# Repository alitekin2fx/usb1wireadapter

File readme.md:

DS2480B Based 1-Wire USB Adapter

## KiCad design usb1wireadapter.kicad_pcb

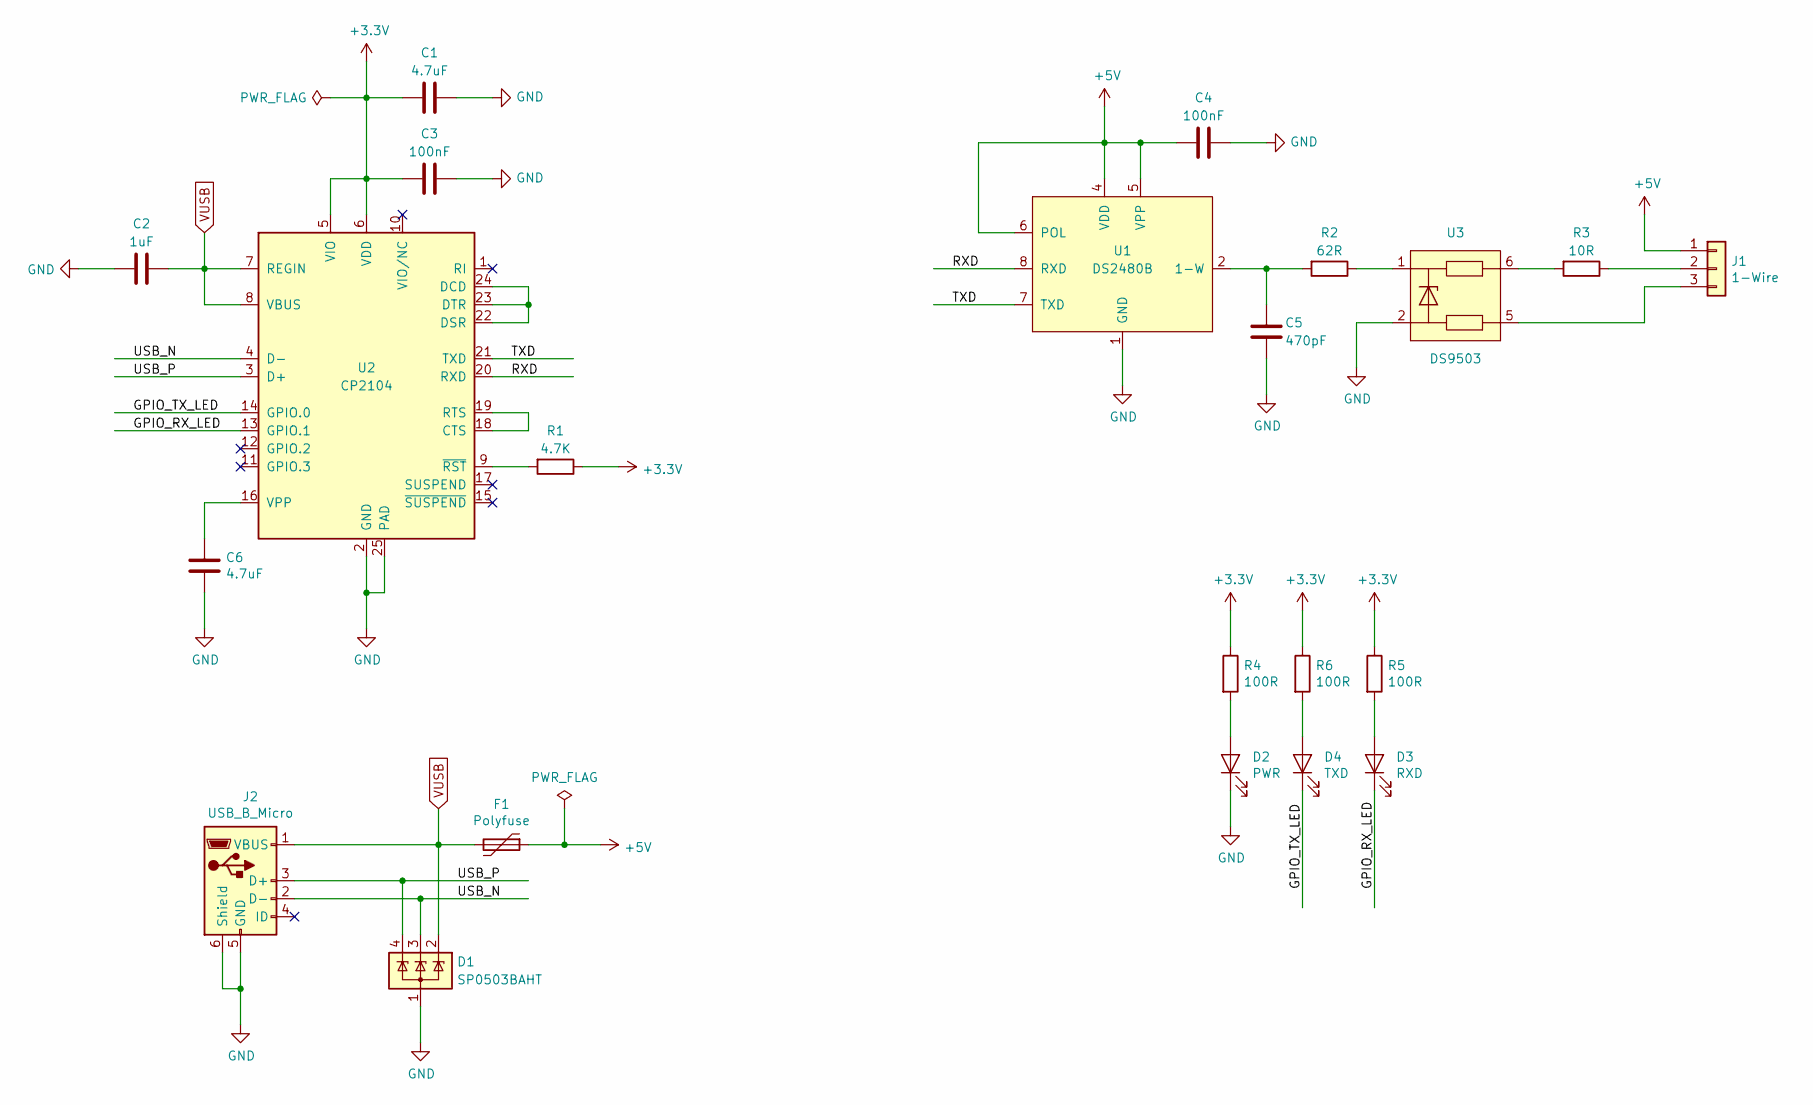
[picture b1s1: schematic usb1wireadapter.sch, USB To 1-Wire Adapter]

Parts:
C1, C6: 4.7uF; C_0805_2012Metric
C2: 1uF; C_0603_1608Metric
C3, C4: 100nF; C_0603_1608Metric
C5: 470pF; C_0603_1608Metric
D1: SP0503BAHT; SOT-143
D2: PWR; LED_0603_1608Metric
D3: RXD; LED_0603_1608Metric
D4: TXD; LED_0603_1608Metric
F1: Polyfuse; Fuse_1206_3216Metric
J1: 1-Wire; JST_XH_B03B-XH-A_1x03_P2.50mm_Vertical
J2: USB_B_Micro; USB_Micro-B_Molex-105017-0001
R1: 4.7K; R_0603_1608Metric
R2: 62R; R_0603_1608Metric
R3: 10R; R_0603_1608Metric
R4, R5, R6: 100R; R_0603_1608Metric
U1: DS2480B; SO-8_5.3x6.2mm_P1.27mm
U2: CP2104; QFN-24-1EP_4x4mm_P0.5mm_EP2.6x2.6mm
U3: DS9503; TSOC-6

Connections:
+3V3: C1.2, C3.2, R1.1, R4.1, R5.1, R6.1, U2.5 (VIO), U2.6 (VDD)
+5V: C4.2, F1.1, J1.1, U1.4 (VDD), U1.5 (VPP), U1.6 (POL)
/GPIO_RX_LED: D3.1 (K), U2.13 (GPIO.1)
/GPIO_TX_LED: D4.1 (K), U2.14 (GPIO.0)
/RXD: U1.8 (RXD), U2.20 (RXD)
/TXD: U1.7 (TXD), U2.21 (TXD)
/USB_N: D1.3 (K), J2.2 (D-), U2.4 (D-)
/USB_P: D1.4 (K), J2.3 (D+), U2.3 (D+)
GND: C1.1, C2.2, C3.1, C4.1, C5.2, C6.2, D1.1 (A), D2.1 (K), J2.5 (GND), J2.6 (Shield), U1.1 (GND), U2.2 (GND), U2.25 (PAD), U3.2
unnamed: C5.1, R2.2, U1.2 (1-W)
unnamed: C6.1, U2.16 (VPP)
unnamed: D2.2 (A), R4.2
unnamed: D3.2 (A), R5.2
unnamed: D4.2 (A), R6.2
unnamed: J1.2, R3.1
unnamed: J1.3, U3.5
unnamed: R1.2, U2.9 (~RST)
unnamed: R2.1, U3.1
unnamed: R3.2, U3.6
unnamed: U2.18 (CTS), U2.19 (RTS)
unnamed: U2.22 (DSR), U2.23 (DTR), U2.24 (DCD)
VUSB: C2.1, D1.2 (K), F1.2, J2.1 (VBUS), U2.7 (REGIN), U2.8 (VBUS)

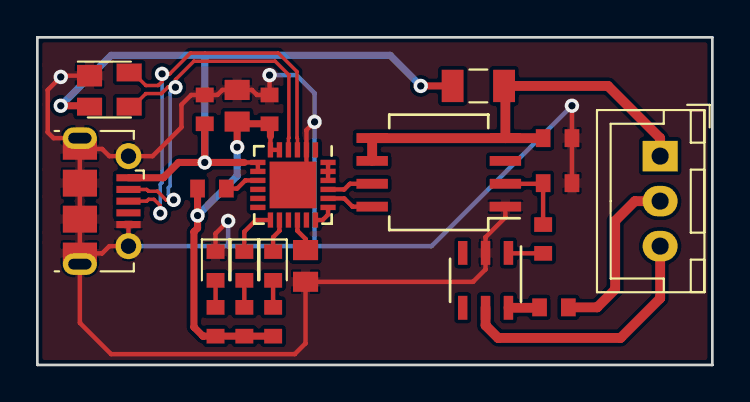
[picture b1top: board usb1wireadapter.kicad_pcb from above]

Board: 2 copper layers, 37.5 x 18.2 mm, 22 parts (0 on the bottom side), 22 nets.
